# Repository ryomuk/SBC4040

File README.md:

# SBC4040
Single Board Computer using Intel 4040

This document is written mostly in Japanese.
If necessary, please use a translation service such as DeepL (I recommend this) or Google.

## 概要
CPUにIntel 4040を採用したシングルボードコンピュータです．4004実験用ボードをベースにして作りました．4004版と完全上位互換なはず．4040の代わりに4004も載せられるようにしてあります．(絶対に同時には搭載しないこと!)

4040にすることによって追加された機能は下記の通りです．

- ROM領域が4KBから8KBに増加
- サブルーチンコールが3段から7段に増加
- PMR命令により，プログラム領域のRAMを直接読めるようになったはず(未確認)
- 割り込み機能
- ステップ実行は使い道が無さそうなので端子だけ出して未実装

## ToDo
- 割り込み機能の動作確認
- 拡張ROM領域(CMROM1)の動作確認
- PMR命令の動作確認
- モニタプログラム，VTL, 8080エミュレータ等を4040用にリライト

## ブログ
関連する情報が書いてあるかも．
- [Intel 4004関連記事のまとめ](https://note.com/ryomuk/m/m2f55e2a1f586)

## 動画
Youtubeで関連動画を公開しています．
- https://www.youtube.com/@ryomukai/videos

## 参考にした文献，サイト
### データシート
- http://www.bitsavers.org/components/intel/
- https://www.intel-vintage.info/intelmcs.htm

### ソフトウェア開発環境
- [The Macroassembler AS](http://john.ccac.rwth-aachen.de:8000/as/)

## 更新履歴
- 2024/2/22: 初版公開

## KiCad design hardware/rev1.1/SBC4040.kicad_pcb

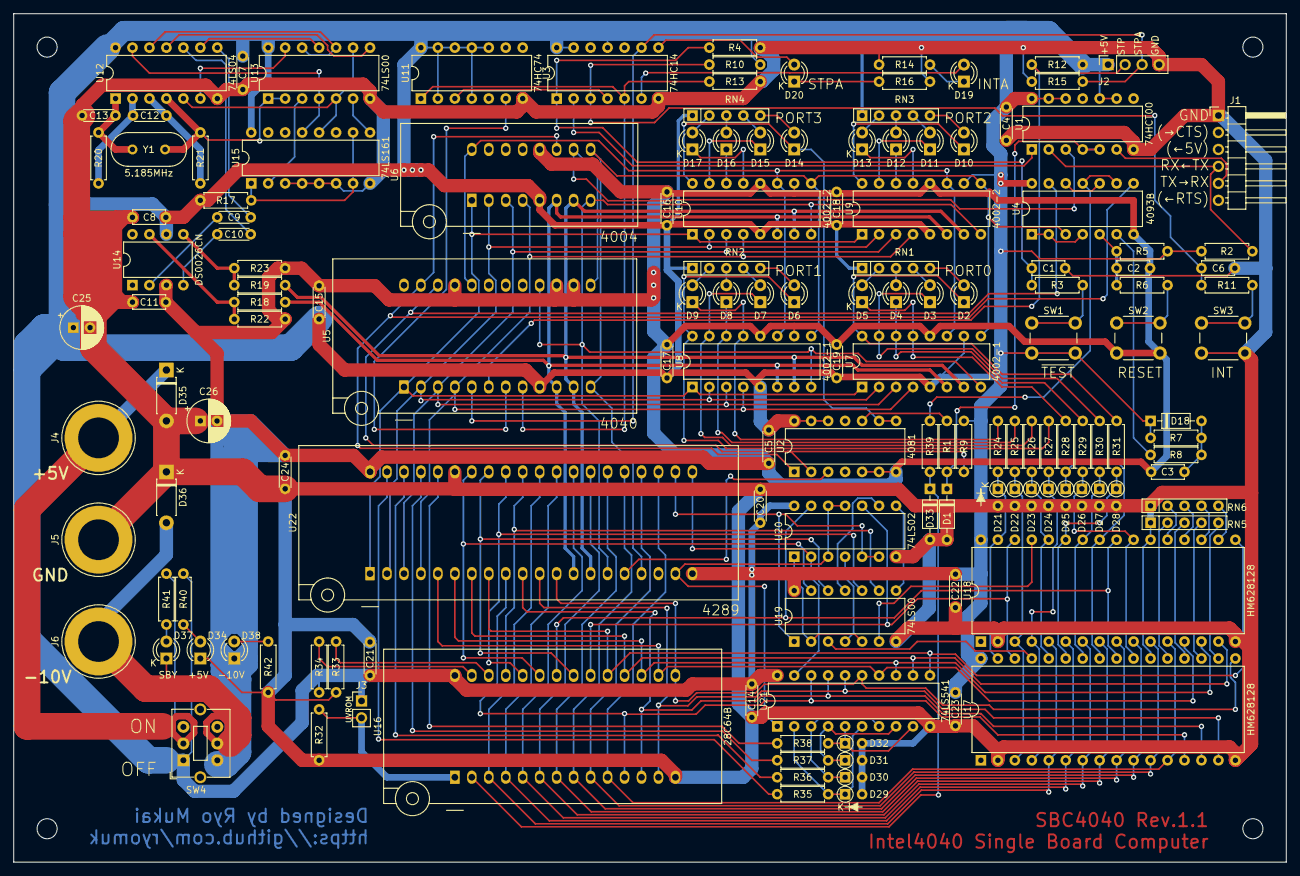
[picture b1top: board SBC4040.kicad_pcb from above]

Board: 2 copper layers, 190.5 x 127.0 mm, 149 parts (0 on the bottom side), 156 nets.

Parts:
C1, C2, C6, C8, C11: 1uF; C_Disc_D4.7mm_W2.5mm_P5.00mm
C3: 10uF; C_Disc_D4.7mm_W2.5mm_P5.00mm
C4, C5, C7, C14, C15, C16, C17, C18, C19, C20, C21, C22, C23, C24: 0.1uF; C_Disc_D4.3mm_W1.9mm_P5.00mm
C9, C10, C12: 0.01uF; C_Disc_D4.3mm_W1.9mm_P5.00mm
C13: 50pF; C_Disc_D4.3mm_W1.9mm_P5.00mm
C25, C26: 47uF; CP_Radial_D6.3mm_P2.50mm
D1, D18, D33: 1N4148; D_DO-35_SOD27_P7.62mm_Horizontal
D2, D3, D4, D5, D6, D7, D8, D9, D10, D11, D12, D13, D14, D15, D16, D17: LED; LED_D3.0mm
D19: INTA; LED_D3.0mm
D20: STPA; LED_D3.0mm
D21, D22, D23, D24, D25, D26, D27, D28, D29, D30, D31, D32: 1N4148; D_DO-35_SOD27_P2.54mm_Vertical_AnodeUp
D34: LED(5V); LED_D3.0mm
D35: 1N4735; D_DO-41_SOD81_P7.62mm_Horizontal
D36: 1N4742; D_DO-41_SOD81_P7.62mm_Horizontal
D37: LED(SBY); LED_D3.0mm
D38: LED(-10V); LED_D3.0mm
H1, H2, H3, H4: MountingHole; MountingHole_3mm
J1: UART(TTL); PinHeader_1x06_P2.54mm_Horizontal
J2: STEP; PinSocket_1x04_P2.54mm_Vertical
J3: UVROM; PinHeader_1x02_P2.54mm_Vertical
J4: +5V; Banana_Jack_1Pin
J5: GND; Banana_Jack_1Pin
J6: -10V; Banana_Jack_1Pin
R1, R2, R4, R5, R10, R12, R24, R25, R26, R27, R28, R29, R30, R31, R39: 10k; R_Axial_DIN0207_L6.3mm_D2.5mm_P7.62mm_Horizontal
R3, R6, R8, R11, R17: 1k; R_Axial_DIN0207_L6.3mm_D2.5mm_P7.62mm_Horizontal
R7, R9, R14, R16, R32, R33, R34, R40, R41, R42: 100k; R_Axial_DIN0207_L6.3mm_D2.5mm_P7.62mm_Horizontal
R13, R15: 12k; R_Axial_DIN0207_L6.3mm_D2.5mm_P7.62mm_Horizontal
R18, R19: 110; R_Axial_DIN0207_L6.3mm_D2.5mm_P7.62mm_Horizontal
R20, R21: 820; R_Axial_DIN0207_L6.3mm_D2.5mm_P7.62mm_Horizontal
R22, R23: 5.6k; R_Axial_DIN0207_L6.3mm_D2.5mm_P7.62mm_Horizontal
R35, R36, R37, R38: 4.7k; R_Axial_DIN0207_L6.3mm_D2.5mm_P7.62mm_Horizontal
RN1, RN2, RN3, RN4, RN5, RN6: 100k; R_Array_SIP5
SW1: ~{TEST}; SW_PUSH_6mm_H4.3mm
SW2: RESET; SW_PUSH_6mm_H4.3mm
SW3: INT; SW_PUSH_6mm_H4.3mm
SW4: SW_DPDT; SW_DPDT_Toggle_with_mount
U1: 74HCT00; DIP-14_W7.62mm
U2: 4081; DIP-14_W7.62mm
U3: 74HC14; DIP-14_W7.62mm
U4: 4093B; DIP-14_W7.62mm
U5: 4040_CPU; DIP_Socket-24_W11.9_W12.7_W15.24_W17.78_W18.5_3M_224-1275-0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
U6: 4004_CPU; DIP_Socket-16_W4.3_W5.08_W7.62_W10.16_W10.9_3M_216-3340-00-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
U7, U8: 4002-1; DIP-16_W7.62mm
U9, U10: 4002-2; DIP-16_W7.62mm
U11: 74HC74; DIP-14_W7.62mm
U12: 74LS04; DIP-14_W7.62mm
U13, U19: 74LS00; DIP-14_W7.62mm
U14: DS0026CN; DIP-8_W7.62mm
U15: 74LS161; DIP-16_W7.62mm
U16: 28C64B; DIP_Socket-28_W11.9_W12.7_W15.24_W17.78_W18.5_3M_228-1277-0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
U17, U18: HM628128; DIP-32_W15.24mm
U20: 74LS02; DIP-14_W7.62mm
U21: 74LS541; DIP-20_W7.62mm
U22: 4289_MEMORY_IF; DIP_Socket-40_W11.9_W12.7_W15.24_W17.78_W18.5_3M_240-1280-0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
Y1: 5.185MHz; Crystal_HC49-U_Vertical

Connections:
+5V: C4.1, C5.2, C7.1, C8.2, C14.1, C15.1, C16.1, C17.1, C18.1, C19.1, C20.1, C21.1, C22.1, C23.1, C25.1, D18.1 (K), J2.1, J3.1, R2.1, R5.2, R7.1, R9.1, R10.1, R12.1, R17.2, R34.2, R40.1, RN1.1 (common), RN2.1 (common), RN3.1 (common), RN4.1 (common), SW1.1, SW4.1 (A), U1.9, U1.10, U1.12, U1.13, U1.14 (VCC), U2.12, U2.13, U2.14 (VDD), U3.11, U3.13, U3.14 (VCC), U4.14 (Vdd), U5.9 (Vss), U6.5 (Vss), U7.5 (Vss), U7.10 (P0), U8.5 (Vss), U9.5 (Vss), U9.10 (P0), U10.5 (Vss), U11.2 (D), U11.4 (~S), U11.10 (~S), U11.11 (C), U11.12 (D), U11.13 (~R), U11.14 (VCC), U12.14 (VCC), U13.14 (VCC), U14.6 (V+), U15.16 (VCC), U16.28 (Vdd), U17.32 (Vcc), U18.32 (Vcc), U19.14 (VCC), U20.14 (VCC), U21.20 (VCC), U22.20 (Vss)
-10V: C2.2, C3.2, C5.1, C11.2, C15.2, C16.2, C17.2, C18.2, C19.2, C24.2, C26.2, D38.1 (K), R22.1, R23.1, SW2.1, SW4.4 (A), U2.5, U2.6, U2.7 (VSS), U4.7 (Vss), U5.14 (Vdd), U5.15 (Vdd2), U5.21 (Vdd1), U6.12 (Vdd), U7.12 (Vdd), U8.10 (P0), U8.12 (Vdd), U9.12 (Vdd), U10.10 (P0), U10.12 (Vdd), U14.3 (V-), U22.40 (Vdd)
/ClockGen/CLK1: R18.2, U5.10 (CLK1), U6.6 (CLK1), U7.6 (CLK1), U8.6 (CLK1), U9.6 (CLK1), U10.6 (CLK1), U22.13 (CLK1)
/ClockGen/CLK2: R19.2, U5.11 (CLK2), U6.7 (CLK2), U7.7 (CLK2), U8.7 (CLK2), U9.7 (CLK2), U10.7 (CLK2), U22.14 (CLK2)
/ProgramMemory/CMROM0: U2.1, U4.8, U5.23 (CMROM0), U6.11 (CMROM)
/ProgramMemory/CMROM1: R9.2, U2.2, U4.13, U5.22 (CMROM1)
/ProgramMemory/D0: U5.1 (D0), U6.1 (D0), U7.1 (D0), U8.1 (D0), U9.1 (D0), U10.1 (D0), U22.1 (D0)
/ProgramMemory/D1: U5.2 (D1), U6.2 (D1), U7.2 (D1), U8.2 (D1), U9.2 (D1), U10.2 (D1), U22.2 (D1)
/ProgramMemory/D2: U5.3 (D2), U6.3 (D2), U7.3 (D2), U8.3 (D2), U9.3 (D2), U10.3 (D2), U22.3 (D2)
/ProgramMemory/D3: U5.4 (D3), U6.4 (D3), U7.4 (D3), U8.4 (D3), U9.4 (D3), U10.4 (D3), U22.4 (D3)
/ProgramMemory/RESET: U4.3, U5.12 (RESET), U6.9 (RESET), U7.9 (RESET), U8.9 (RESET), U9.9 (RESET), U10.9 (RESET), U22.17 (RESET)
/ProgramMemory/SYNC: U5.16 (SYNC), U6.8 (SYNC), U7.8 (SYNC), U8.8 (SYNC), U9.8 (SYNC), U10.8 (SYNC), U22.15 (SYNC)
A0: U16.10 (A0), U17.12 (A0), U18.12 (A0), U22.23 (A0)
A1: U16.9 (A1), U17.11 (A1), U18.11 (A1), U22.24 (A1)
A2: U16.8 (A2), U17.10 (A2), U18.10 (A2), U22.25 (A2)
A3: U16.7 (A3), U17.9 (A3), U18.9 (A3), U22.26 (A3)
A4: U16.6 (A4), U17.8 (A4), U18.8 (A4), U22.27 (A4)
A5: U16.5 (A5), U17.7 (A5), U18.7 (A5), U22.28 (A5)
A6: U16.4 (A6), U17.6 (A6), U18.6 (A6), U22.29 (A6)
A7: U16.3 (A7), U17.5 (A7), U18.5 (A7), U22.30 (A7)
A8: D28.1 (K), R31.2, U17.27 (A8), U18.27 (A8)
A9: D27.1 (K), R30.2, U17.26 (A9), U18.26 (A9)
A10: D26.1 (K), R29.2, U17.23 (A10), U18.23 (A10)
A11: D25.1 (K), R28.2, U17.25 (A11), U18.25 (A11)
A12: D24.1 (K), R27.2, U17.4 (A12), U18.4 (A12)
A13: D23.1 (K), R26.2, U17.28 (A13), U18.28 (A13)
A14: D22.1 (K), R25.2, U17.3 (A14), U18.3 (A14)
A15: D21.1 (K), R24.2, U17.31 (A15), U18.31 (A15)
BANK0: D2.1 (K), R31.1, U7.16 (O0)
BANK1: D3.1 (K), R30.1, U7.15 (O1)
BANK2: D4.1 (K), R29.1, U7.14 (O2)
BANK3: D5.1 (K), R28.1, U7.13 (O3)
BANK4: D6.1 (K), R27.1, U8.16 (O0)
BANK5: D7.1 (K), R26.1, U8.15 (O1)
BANK6: D8.1 (K), R25.1, U8.14 (O2)
BANK7: D9.1 (K), R24.1, U8.13 (O3)
C0: U16.25 (A8), U19.9, U22.31 (C0)
C1: U16.24 (A9), U19.10, U22.32 (C1)
C2: U16.21 (A10), U19.12, U22.33 (C2)
C3: U16.23 (A11), U19.13, U22.34 (C3)
CS~ROMRAM: U16.20 (~CS), U17.30 (CS2), U18.30 (CS2), U20.10
GND: C1.2, C4.2, C6.2, C7.2, C8.1, C11.1, C13.2, C14.2, C20.2, C21.2, C22.2, C23.2, C24.1, C25.2, C26.1, D1.2 (A), D21.2 (A), D22.2 (A), D23.2 (A), D24.2 (A), D25.2 (A), D26.2 (A), D27.2 (A), D28.2 (A), D29.2 (A), D30.2 (A), D31.2 (A), D32.2 (A), D33.2 (A), D34.1 (K), D35.2 (A), D36.1 (K), J1.1, J2.4, J5.1, R4.2, R13.2, R14.2, R15.2, R16.2, R32.1, R33.1, R42.1, RN5.1 (common), RN6.1 (common), SW3.1, U1.7 (GND), U3.7 (GND), U11.7 (GND), U12.7 (GND), U13.7 (GND), U15.3 (A), U15.4 (B), U15.5 (C), U15.6 (D), U15.8 (GND), U16.14 (Vss(GND)), U17.2 (A16), U17.16 (Vss(GND)), U17.22 (~CS1), U18.2 (A16), U18.16 (Vss(GND)), U18.22 (~CS1), U19.7 (GND), U20.7 (GND), U21.10 (GND), U22.35 (Vdd1)
INT: U5.7 (INT), U11.6 (~Q)
INTA: R13.1, U3.5, U5.8 (INTA), U11.1 (~R)
IO1: R35.1, U22.39 (I/O1)
IO2: R36.1, U22.38 (I/O2)
IO3: R37.1, U22.37 (I/O3)
IO4: R38.1, U22.36 (I/O4)
unnamed: C1.1, R3.2, R4.1, U3.1
unnamed: C2.1, R5.1, R6.2, U4.5
unnamed: C6.1, R10.2, R11.2, U3.3
unnamed: C9.1, U12.8
unnamed: C10.1, U12.10
unnamed: C12.1, R20.2, U12.2
unnamed: C12.2, R21.1, U12.3
unnamed: C13.1, R20.1, U12.1, Y1.1
unnamed: D1.1 (K), R1.1, U1.4, U1.5
unnamed: D2.2 (A), RN1.5 (R4)
unnamed: D3.2 (A), RN1.4 (R3)
unnamed: D4.2 (A), RN1.3 (R2)
unnamed: D5.2 (A), RN1.2 (R1)
unnamed: D6.2 (A), RN2.5 (R4)
unnamed: D7.2 (A), RN2.4 (R3)
unnamed: D8.2 (A), RN2.3 (R2)
unnamed: D9.2 (A), RN2.2 (R1)
unnamed: D10.2 (A), RN3.5 (R4)
unnamed: D10.1 (K), U9.16 (O0)
unnamed: D11.2 (A), RN3.4 (R3)
unnamed: D11.1 (K), U9.15 (O1)
unnamed: D12.2 (A), RN3.3 (R2)
unnamed: D12.1 (K), U9.14 (O2)
unnamed: D13.2 (A), RN3.2 (R1)
unnamed: D13.1 (K), U9.13 (O3)
unnamed: D14.2 (A), RN4.5 (R4)
unnamed: D14.1 (K), U2.8, U2.9, U10.16 (O0)
unnamed: D15.2 (A), RN4.4 (R3)
unnamed: D15.1 (K), U10.15 (O1)
unnamed: D16.2 (A), RN4.3 (R2)
unnamed: D16.1 (K), U10.14 (O2)
unnamed: D17.2 (A), RN4.2 (R1)
unnamed: D17.1 (K), U10.13 (O3)
unnamed: C3.1, D18.2 (A), R7.2, R8.1
unnamed: D19.2 (A), U3.6
unnamed: D19.1 (K), R14.1
unnamed: D20.2 (A), U3.8
unnamed: D20.1 (K), R16.1
unnamed: D29.1 (K), R35.2, U21.2 (A0), U21.6 (A4)
unnamed: D30.1 (K), R36.2, U21.3 (A1), U21.7 (A5)
unnamed: D31.1 (K), R37.2, U21.4 (A2), U21.8 (A6)
unnamed: D32.1 (K), R38.2, U21.5 (A3), U21.9 (A7)
unnamed: D34.2 (A), R40.2
unnamed: D35.1 (K), J4.1, R41.1, SW4.2 (B)
unnamed: D36.2 (A), D37.1 (K), J6.1, SW4.5 (B)
unnamed: D37.2 (A), R41.2
unnamed: D38.2 (A), R42.2
unnamed: J1.4, R2.2, U1.2
unnamed: J1.5, U1.6
unnamed: R1.2, U2.10
unnamed: R3.1, SW1.2
unnamed: R6.1, SW2.2
unnamed: R8.2, U4.6
unnamed: R11.1, SW3.2
unnamed: R21.2, U12.4, U13.1, U13.2, Y1.2
unnamed: R39.1, U4.9, U4.11
unnamed: RN5.2 (R1), U17.21 (I/O7)
unnamed: RN5.3 (R2), U17.20 (I/O6)
unnamed: RN5.4 (R3), U17.19 (I/O5)
unnamed: RN5.5 (R4), U17.18 (I/O4)
unnamed: RN6.2 (R1), U18.21 (I/O7)
unnamed: RN6.3 (R2), U18.20 (I/O6)
unnamed: RN6.4 (R3), U18.19 (I/O5)
unnamed: RN6.5 (R4), U18.18 (I/O4)
unnamed: U1.1, U3.2
unnamed: U4.1, U4.2, U4.4
unnamed: U4.10, U4.12
unnamed: U1.3, U5.13 (TEST), U6.10 (TEST)
unnamed: U5.20 (CMRAM0), U6.16 (CMRAM0), U7.11 (CM), U8.11 (CM), U9.11 (CM), U10.11 (CM)
unnamed: U3.4, U11.3 (C)
unnamed: U12.6, U13.13
unnamed: U12.9, U13.11
unnamed: U12.11, U13.8
unnamed: U12.12, U13.10, U13.12
unnamed: C9.2, U14.2 (IN_A)
unnamed: C10.2, U14.4 (IN_B)
unnamed: R18.1, R22.2, U14.7 (OUT_A)
unnamed: R19.1, R23.2, U14.5 (OUT_B)
unnamed: U13.3, U15.2 (CLOCK)
unnamed: R17.1, U15.1 (~CLEAR), U15.7 (EP), U15.10 (ET)
unnamed: U13.6, U15.9 (LOAD)
unnamed: U12.13, U13.4, U15.13 (QB)
unnamed: U12.5, U13.5, U13.9, U15.12 (QC)
unnamed: U19.2, U19.5, U20.1
unnamed: U19.4, U20.4
unnamed: U19.8, U20.8
unnamed: U19.11, U20.9
unnamed: U20.3, U20.11, U20.12, U21.1 (G1), U22.19 (OUT)
unnamed: U20.2, U21.19 (G2), U22.21 (PM)
unnamed: U2.3, U22.16 (CM)
unnamed: U19.1, U20.5, U20.6, U22.22 (FL)
OPA0: U16.11 (D0), U17.13 (I/O0), U21.18 (Y0), U22.9 (OPA0)
OPA1: U16.12 (D1), U17.14 (I/O1), U21.17 (Y1), U22.10 (OPA1)
OPA2: U16.13 (D2), U17.15 (I/O2), U21.16 (Y2), U22.11 (OPA2)
OPA3: U16.15 (D3), U17.17 (I/O3), U21.15 (Y3), U22.12 (OPA3)
OPR0: U16.16 (D4), U18.13 (I/O0), U21.14 (Y4), U22.5 (OPR0)
OPR1: U16.17 (D5), U18.14 (I/O1), U21.13 (Y5), U22.6 (OPR1)
OPR2: U16.18 (D6), U18.15 (I/O2), U21.12 (Y6), U22.7 (OPR2)
OPR3: U16.19 (D7), U18.17 (I/O3), U21.11 (Y7), U22.8 (OPR3)
ROM_A12: D33.1 (K), R39.2, U16.2 (A12)
ROM_P1: J3.2, R32.2, U16.1 (NC)
ROM_P26: R33.2, U16.26 (NC)
ROM_P27: R34.1, U16.27 (~WE)
STP: J2.2, R12.2, U5.6 (STP)
STPA: J2.3, R15.1, U3.9, U5.5 (STPA)
~OE: U16.22 (~OE), U17.24 (~OE), U18.24 (~OE), U20.13
~WE_OPA: U17.29 (~WE), U19.3
~WE_OPR: U18.29 (~WE), U19.6
